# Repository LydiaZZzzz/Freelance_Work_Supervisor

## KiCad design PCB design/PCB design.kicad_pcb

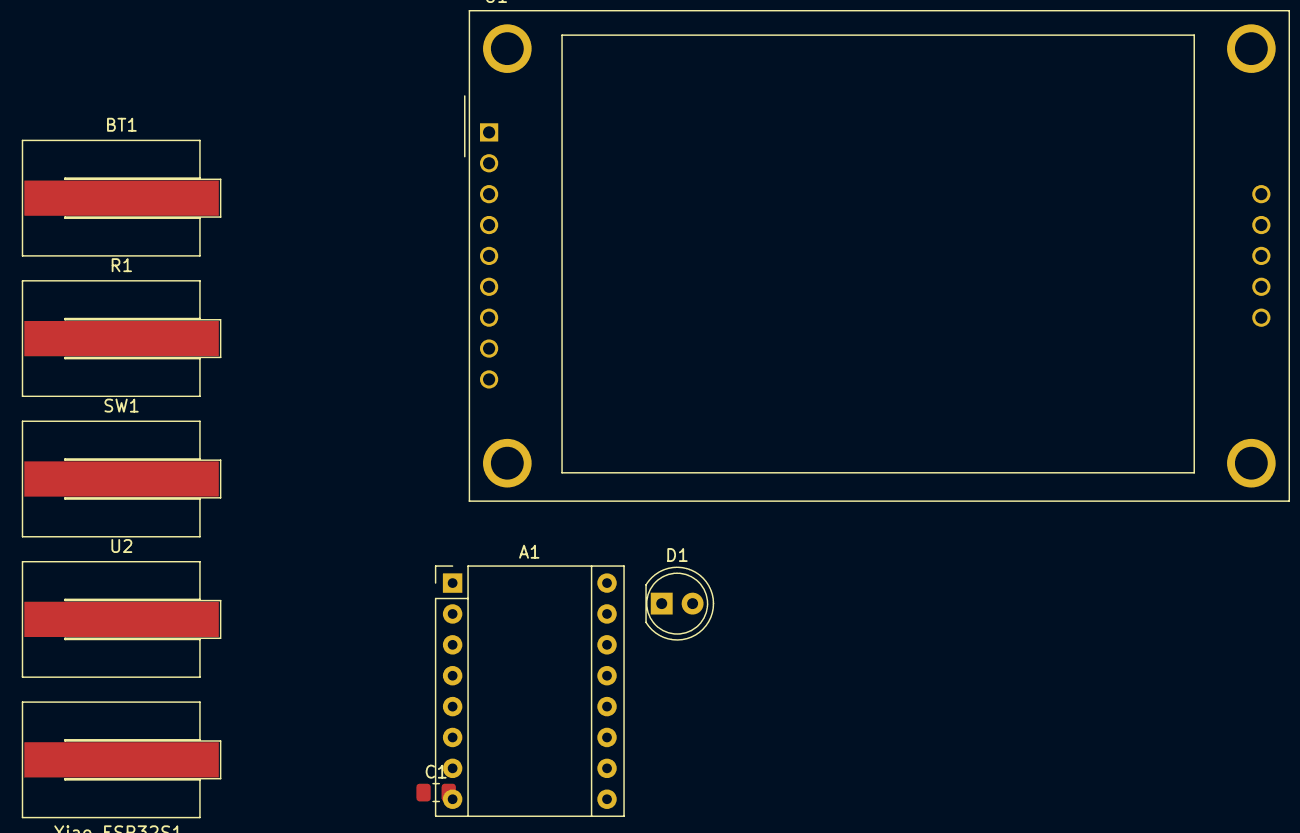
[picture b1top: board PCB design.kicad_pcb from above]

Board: 2 copper layers, 9 parts (0 on the bottom side), 4 nets, no tracks yet.

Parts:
A1: Pololu_Breakout_A4988; Pololu_Breakout-16_15.2x20.3mm
BT1: Battery_Cell; BatteryHolder_Keystone_2993
C1: 10uF; C_0805_2012Metric_Pad1.18x1.45mm_HandSolder
D1: LD271; LED_D5.0mm_IRGrey
R1: 330Ω; BatteryHolder_Keystone_2993
SW1: SW_MEC_5E; BatteryHolder_Keystone_2993
U1: CR2013-MI2120
U2: OV2640; BatteryHolder_Keystone_2993
Xiao_ESP32S1: BatteryHolder_Keystone_2993

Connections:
/GND: A1.1 (GND), D1.2 (A), SW1.1, U1.2 (GND)
/SCL: A1.15 (STEP), U2.1
unnamed: A1.8 (VMOT), C1.1
unnamed: BT1.1 (+), C1.2

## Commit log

2025-01-22 Reset repository
2025-01-22 System Architecture with Diagram
